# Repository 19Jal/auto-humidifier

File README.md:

# auto-humidifier
A little project I made for my Embedded Systems class in college

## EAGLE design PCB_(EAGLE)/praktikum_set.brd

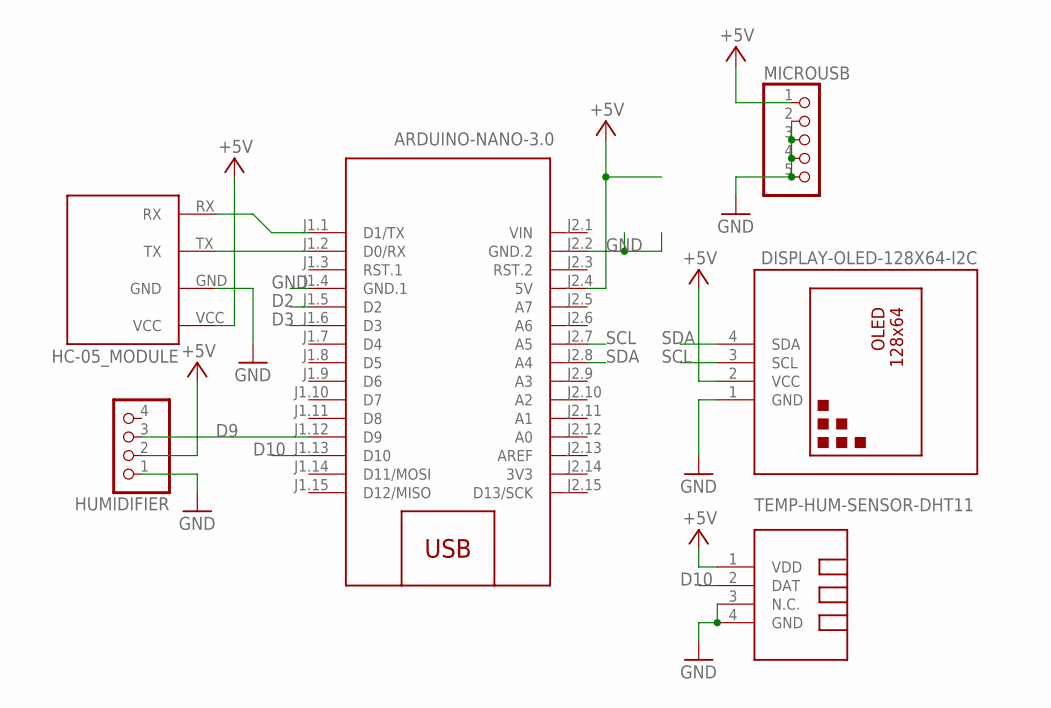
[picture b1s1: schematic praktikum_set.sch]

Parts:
DHT11: TEMP-HUM-SENSOR-DHT11
HC-05_MODULE: BLUETOOTH_BOARDSTANDING; BT_BOARD_FOOTPRINT_STANDING
HUMIDIFIER: PINHD-1X4; 1X04
M1: ARDUINO-NANO-3.0
MICROUSB: PINHD-1X5; 1X05
U$1: DISPLAY-OLED-128X64-I2C

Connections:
3V3: M1.J2.14 (3V3)
+5V: DHT11.1 (VDD), HC-05_MODULE.VCC, HUMIDIFIER.2, M1.J2.4 (5V), MICROUSB.1, U$1.2 (VCC)
D2: M1.J1.5 (D2)
D3: M1.J1.6 (D3)
D9: HUMIDIFIER.3, M1.J1.12 (D9)
D10: DHT11.2 (DAT), M1.J1.13 (D10)
GND: DHT11.3 (N.C.), DHT11.4 (GND), HC-05_MODULE.GND, HUMIDIFIER.1, M1.J1.4 (GND.1), M1.J2.2 (GND.2), MICROUSB.2, MICROUSB.3, MICROUSB.4, MICROUSB.5, U$1.1 (GND)
unnamed: HC-05_MODULE.RX, M1.J1.1 (D1/TX)
unnamed: HC-05_MODULE.TX, M1.J1.2 (D0/RX)
SCL: M1.J2.7 (A5), U$1.3 (SCL)
SDA: M1.J2.8 (A4), U$1.4 (SDA)
VIN: M1.J2.1 (VIN)

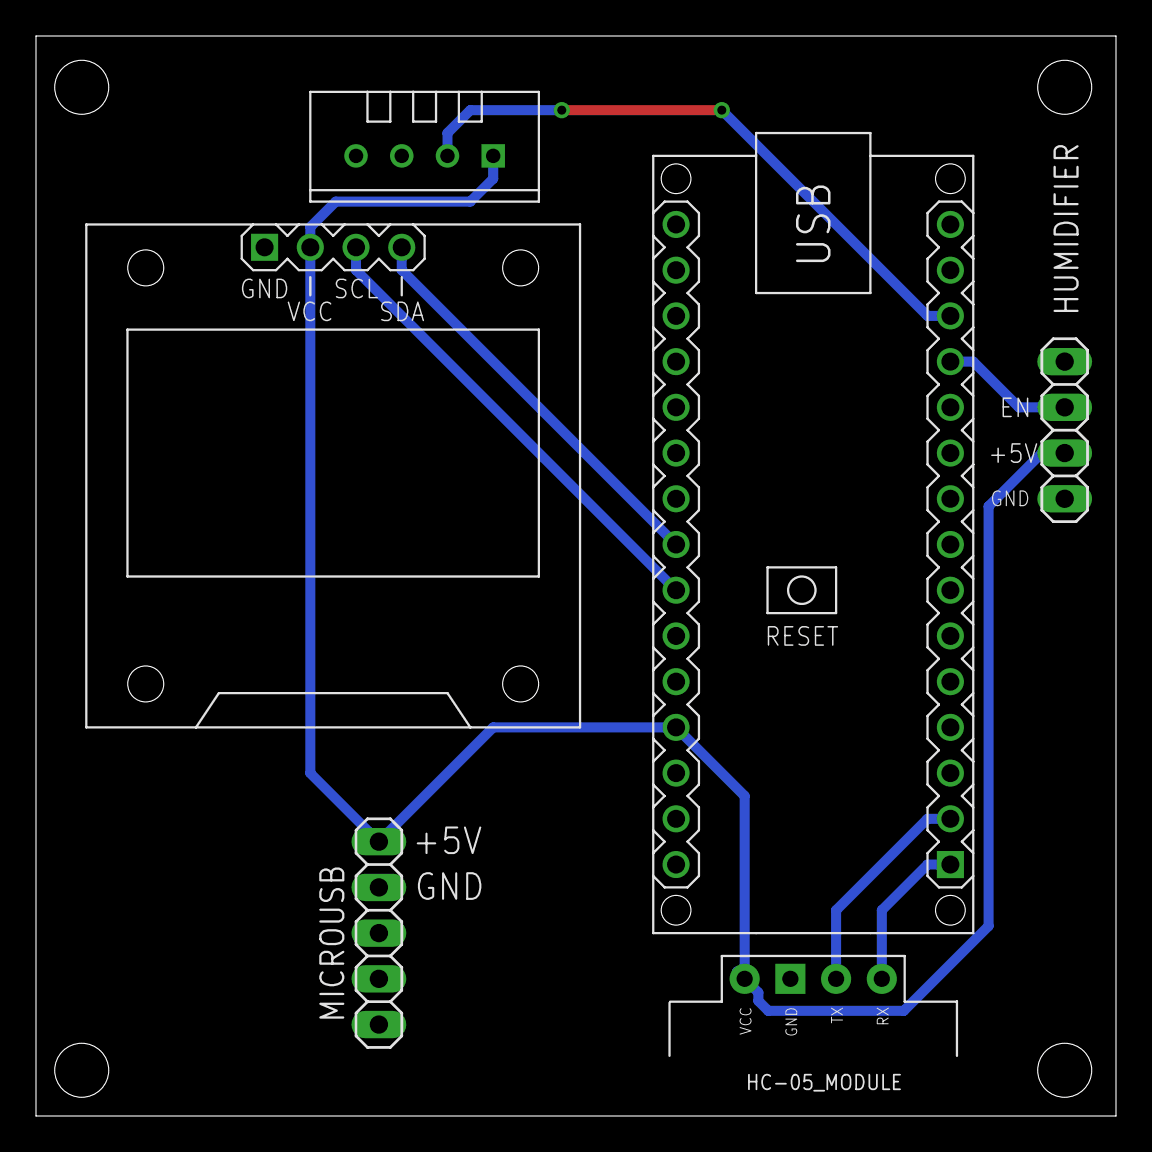
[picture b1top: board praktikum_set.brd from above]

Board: 2 copper layers, 60.0 x 60.0 mm, 6 parts (0 on the bottom side), 8 nets.

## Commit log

2022-10-11 Create s

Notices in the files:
parts and their libraries:
diy-modules: Released under the Creative Commons Attribution 4.0 International License: http://creativecommons.org/licenses/by/4.0
